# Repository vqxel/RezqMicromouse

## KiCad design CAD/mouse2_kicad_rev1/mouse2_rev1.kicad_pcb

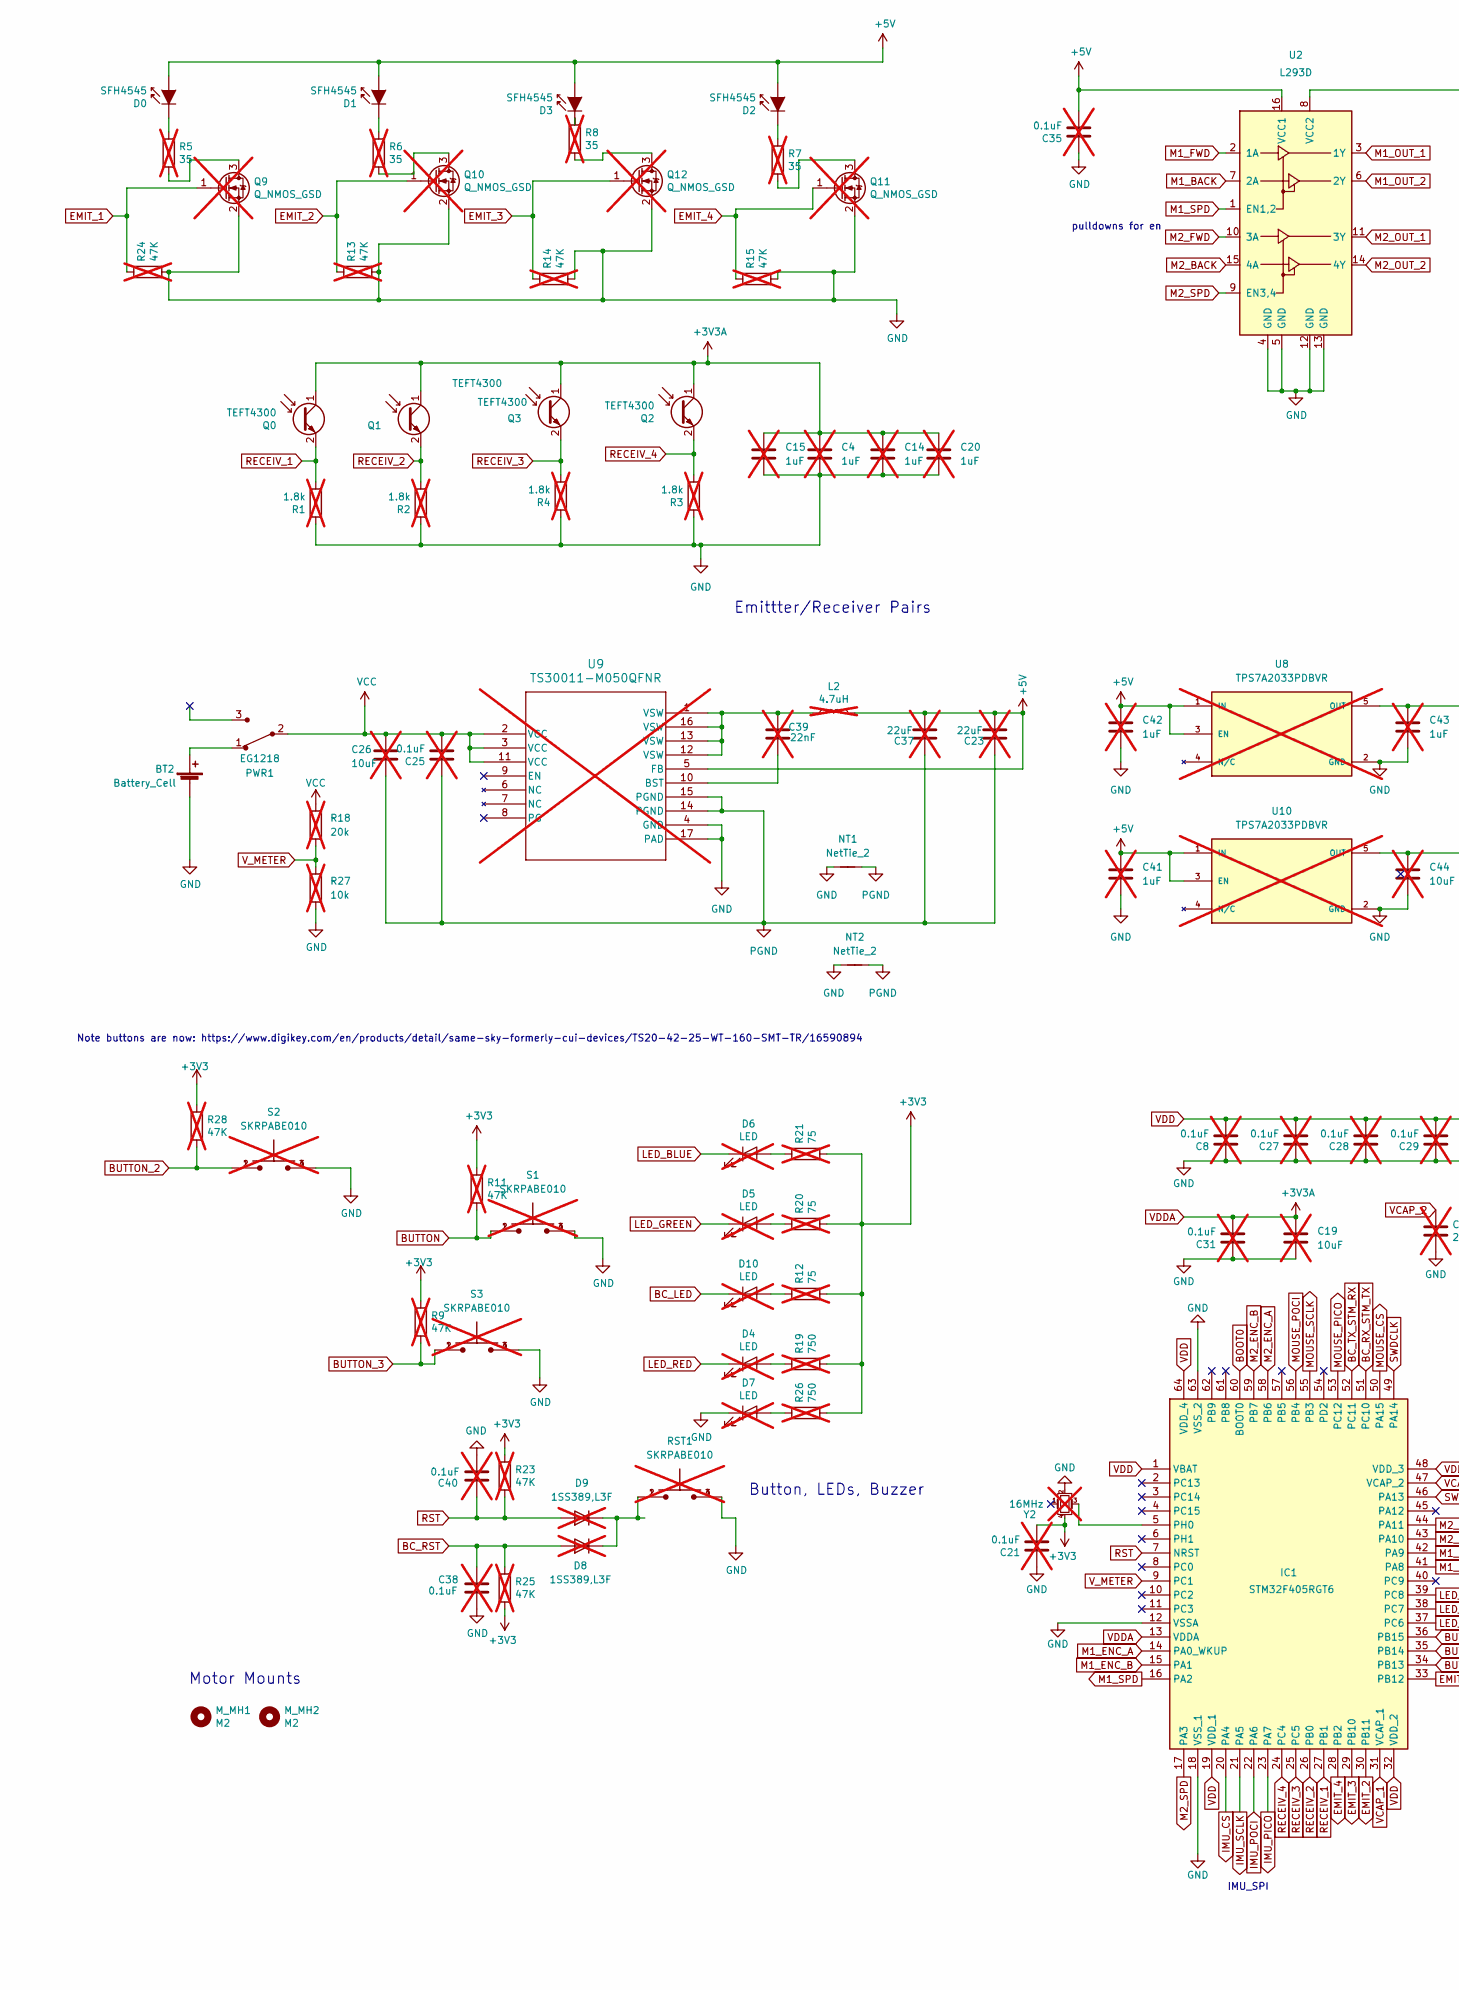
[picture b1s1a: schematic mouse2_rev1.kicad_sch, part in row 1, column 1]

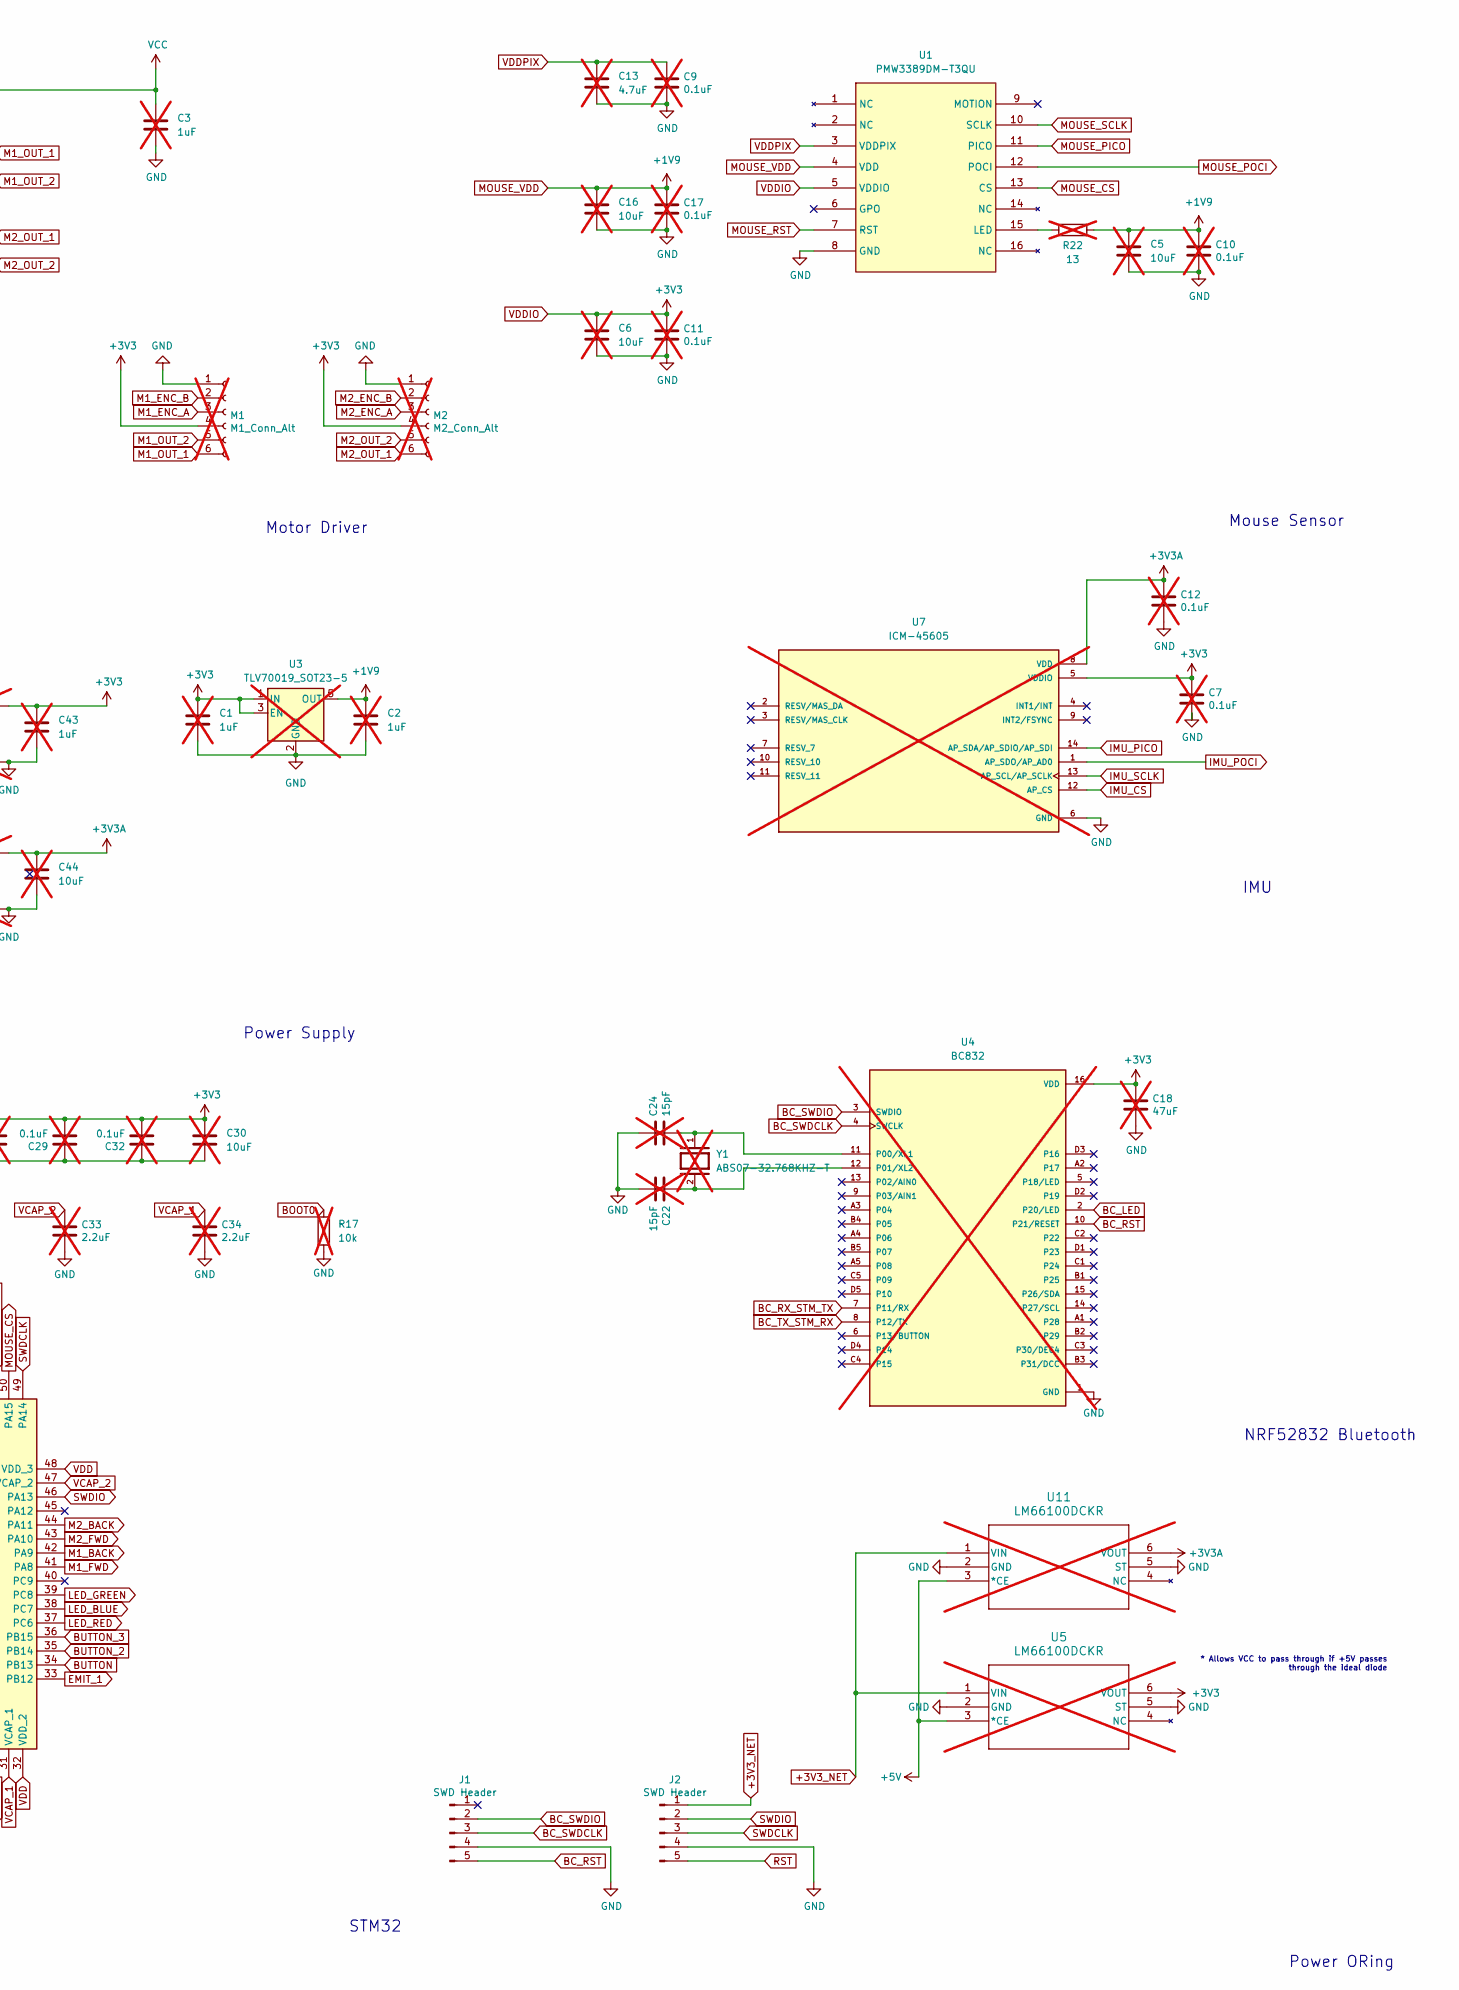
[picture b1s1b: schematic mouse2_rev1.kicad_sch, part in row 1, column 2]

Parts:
BT2: Battery_Cell; PinSocket_1x02_P2.54mm_Vertical
C1, C2, C3, C4, C14, C15, C20, C41, C42, C43: 1uF; C_0603_1608Metric_Pad1.08x0.95mm_HandSolder; not fitted
C5, C6, C16, C19, C26, C30, C44: 10uF; C_0603_1608Metric_Pad1.08x0.95mm_HandSolder; not fitted
C7, C8, C9, C10, C11, C12, C17, C21, C25, C27, C28, C29, C31, C32, C35, C38, C40: 0.1uF; C_0603_1608Metric_Pad1.08x0.95mm_HandSolder; not fitted
C13: 4.7uF; C_0603_1608Metric_Pad1.08x0.95mm_HandSolder; not fitted
C18: 47uF; C_0603_1608Metric_Pad1.08x0.95mm_HandSolder; not fitted
C22, C24: 15pF; C_0603_1608Metric_Pad1.08x0.95mm_HandSolder; not fitted
C23, C37: 22uF; C_0603_1608Metric_Pad1.08x0.95mm_HandSolder; not fitted
C33, C34: 2.2uF; C_0603_1608Metric_Pad1.08x0.95mm_HandSolder; not fitted
C39: 22nF; C_0603_1608Metric_Pad1.08x0.95mm_HandSolder; not fitted
D0, D1, D2, D3: SFH4545; Emitter
D4, D5, D6, D7, D10: LED; LED_0805_2012Metric_Pad1.15x1.40mm_HandSolder; not fitted
D8, D9: 1SS389,L3F; D_SOD-523; not fitted
IC1: STM32F405RGT6; QFP50P1200X1200X160-64N; Manufacturer_Part_Number STM32F405RGT6; Mouser Part Number 511-STM32F405RGT6
J1, J2: SWD Header; PinHeader_1x05_P2.54mm_Vertical
L2: 4.7uH; L_1210_3225Metric_Pad1.42x2.65mm_HandSolder; not fitted
M1: M1_Conn_Alt; JST_SH_BM06B-SRSS-TB_1x06-1MP_P1.00mm_Vertical; not fitted
M2: M2_Conn_Alt; JST_SH_BM06B-SRSS-TB_1x06-1MP_P1.00mm_Vertical; not fitted
M_MH1, M_MH2: M2; Motor_mouse
NT1, NT2: NetTie_2; NetTie-2_SMD_Pad0.5mm
PWR1: EG1218; MM Switch; MPN EG1218; Digi-Key_PN EG1903-ND
Q0, Q1, Q2, Q3: TEFT4300; Emitter
Q9, Q10, Q11, Q12: Q_NMOS_GSD; SOT-23; not fitted
R1, R2, R3, R4: 1.8k; R_0603_1608Metric_Pad0.98x0.95mm_HandSolder; not fitted
R5, R6, R7, R8: 35; R_0603_1608Metric_Pad0.98x0.95mm_HandSolder; not fitted
R9, R11, R13, R14, R15, R23, R24, R25, R28: 47K; R_0603_1608Metric_Pad0.98x0.95mm_HandSolder; not fitted
R12, R20, R21: 75; R_0603_1608Metric_Pad0.98x0.95mm_HandSolder; not fitted
R17, R27: 10k; R_0603_1608Metric_Pad0.98x0.95mm_HandSolder; not fitted
R18: 20k; R_0603_1608Metric_Pad0.98x0.95mm_HandSolder; not fitted
R19, R26: 750; R_0603_1608Metric_Pad0.98x0.95mm_HandSolder; not fitted
R22: 13; R_0603_1608Metric_Pad0.98x0.95mm_HandSolder; not fitted
RST1: SKRPABE010; SW_SKRPABE010; not fitted
S1, S2, S3: SKRPABE010; SW_SKRPABE010; not fitted
U1: PMW3389DM-T3QU; PMW3360DM
U2: L293D; DIP-16_W7.62mm
U3: TLV70019_SOT23-5; SOT-23-5; not fitted
U4: BC832; XCVR_BC832; PARTREV 2.02; not fitted
U5, U11: LM66100DCKR; DCK6_TEX; not fitted
U7: ICM-45605; XDCR_ICM-45605; PARTREV 1.0; DigiKey_Part_Number 1428-ICM-45605CT-ND; not fitted
U8, U10: TPS7A2033PDBVR; SOT95P280X145-5N; PARTREV H; not fitted
U9: TS30011-M050QFNR; QFN16_3X3_SEM; not fitted
Y1: ABS07-32.768KHZ-T; XTAL_ABS07-32.768KHZ-T; PARTREV 08.19.15; not fitted
Y2: 16MHz; Crystal_SMD_2016-4Pin_2.0x1.6mm; Part # ECS-1633-160-BN-TR; not fitted

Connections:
+3V3_NET: J2.1, U5.1 (VIN), U11.1 (VIN)
+5V: C23.1, C35.2, C37.1, C41.1, C42.1, D0.2 (A), D1.2 (A), D2.2 (A), D3.2 (A), L2.2, U2.16 (VCC1), U5.3 (*CE), U8.1 (IN), U8.3 (EN), U9.5 (FB), U10.1 (IN), U10.3 (EN), U11.3 (*CE)
BC_LED: D10.1 (K), U4.2 (P20/LED)
BC_RST: C38.1, D8.2 (A), J1.5, R25.1, U4.10 (P21/RESET)
BC_RX_STM_TX: IC1.51 (PC10), U4.7 (P11/RX)
BC_SWDCLK: J1.3, U4.4 (SWCLK)
BC_SWDIO: J1.2, U4.3 (SWDIO)
BC_TX_STM_RX: IC1.52 (PC11), U4.8 (P12/TX)
BOOT0: IC1.60 (BOOT0), R17.1
BUTTON: IC1.34 (PB13), R11.2, S1.1, S1.2
BUTTON_2: IC1.35 (PB14), R28.2, S2.1, S2.2
BUTTON_3: IC1.36 (PB15), R9.2, S3.1, S3.2
EMIT_1: IC1.33 (PB12), Q9.1 (G), R24.1
EMIT_2: IC1.30 (PB11), Q10.1 (G), R13.1
EMIT_3: IC1.29 (PB10), Q12.1 (G), R14.1
EMIT_4: IC1.28 (PB2), Q11.1 (G), R15.1
GND: BT2.2 (-), C1.2, C2.2, C3.2, C4.2, C5.2, C6.2, C7.2, C8.1, C9.2, C10.2, C11.2, C12.2, C13.2, C14.2, C15.2, C16.2, C17.2, C18.2, C19.2, C20.2, C21.1, C22.2, C24.1, C27.1, C28.1, C29.1, C30.2, C31.1, C32.1, C33.2, C34.2, C35.1, C38.2, C40.2, C41.2, C42.2, C43.2, C44.2, D7.1 (K), IC1.12 (VSSA), IC1.18 (VSS_1), IC1.63 (VSS_2), J1.4, J2.4, M1.1, M2.1, NT1.1, NT2.1, Q9.2 (S), Q10.2 (S), Q11.2 (S), Q12.2 (S), R1.1, R2.1, R3.1, R4.1, R13.2, R14.2, R15.2, R17.2, R24.2, R27.2, RST1.3, RST1.4, S1.3, S1.4, S2.3, S2.4, S3.3, S3.4, U1.8 (GND), U2.4 (GND), U2.5 (GND), U2.12 (GND), U2.13 (GND), U3.2 (GND), U4.1 (GND), U5.2 (GND), U5.5 (ST)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
IMU_CS: IC1.20 (PA4), U7.12 (AP_CS)
IMU_PICO: IC1.23 (PA7), U7.14 (AP_SDA/AP_SDIO/AP_SDI)
IMU_POCI: IC1.22 (PA6), U7.1 (AP_SDO/AP_AD0)
IMU_SCLK: IC1.21 (PA5), U7.13 (AP_SCL/AP_SCLK)
LED_BLUE: D6.1 (K), IC1.38 (PC7)
LED_GREEN: D5.1 (K), IC1.39 (PC8)
LED_RED: D4.1 (K), IC1.37 (PC6)
M1_BACK: IC1.42 (PA9), U2.7 (2A)
M1_ENC_A: IC1.14 (PA0_WKUP), M1.3
M1_ENC_B: IC1.15 (PA1), M1.2
M1_FWD: IC1.41 (PA8), U2.2 (1A)
M1_OUT_1: M1.6, U2.3 (1Y)
M1_OUT_2: M1.5, U2.6 (2Y)
M1_SPD: IC1.16 (PA2), U2.1 (EN1,2)
M2_BACK: IC1.44 (PA11), U2.15 (4A)
M2_ENC_A: IC1.58 (PB6), M2.3
M2_ENC_B: IC1.59 (PB7), M2.2
M2_FWD: IC1.43 (PA10), U2.10 (3A)
M2_OUT_1: M2.6, U2.11 (3Y)
M2_OUT_2: M2.5, U2.14 (4Y)
M2_SPD: IC1.17 (PA3), U2.9 (EN3,4)
MOUSE_CS: IC1.50 (PA15), U1.13 (CS)
MOUSE_PICO: IC1.53 (PC12), U1.11 (PICO)
MOUSE_POCI: IC1.56 (PB4), U1.12 (POCI)
MOUSE_RST: U1.7 (RST)
MOUSE_SCLK: IC1.55 (PB3), U1.10 (SCLK)
MOUSE_VDD: C2.1, C5.1, C10.1, C16.1, C17.1, R22.2, U1.4 (VDD), U3.5 (OUT)
unnamed: BT2.1 (+), PWR1.1
unnamed: C39.2, L2.1, U9.1 (VSW), U9.12 (VSW), U9.13 (VSW), U9.16 (VSW)
unnamed: D0.1 (K), R5.1
unnamed: D1.1 (K), R6.1
unnamed: D2.1 (K), R7.1
unnamed: D3.1 (K), R8.1
unnamed: D4.2 (A), R19.1
unnamed: D5.2 (A), R20.1
unnamed: D6.2 (A), R21.1
unnamed: D7.2 (A), R26.1
unnamed: D8.1 (K), D9.1 (K), RST1.1, RST1.2
unnamed: D10.2 (A), R12.1
unnamed: IC1.5 (PH0), Y2.3
unnamed: Q9.3 (D), R5.2
unnamed: Q10.3 (D), R6.2
unnamed: Q11.3 (D), R7.2
unnamed: Q12.3 (D), R8.2
unnamed: R22.1, U1.15 (LED)
unnamed: C24.2, U4.11 (P00/XL1), Y1.1
unnamed: C22.1, U4.12 (P01/XL2), Y1.2
unnamed: C39.1, U9.10 (BST)
PGND: C23.2, C25.1, C26.2, C37.2, NT1.2, NT2.2, U9.14 (PGND), U9.15 (PGND)
RECEIV_1: IC1.27 (PB1), Q0.2 (E), R1.2
RECEIV_2: IC1.26 (PB0), Q1.2 (E), R2.2
RECEIV_3: IC1.25 (PC5), Q3.2 (E), R4.2
RECEIV_4: IC1.24 (PC4), Q2.2 (E), R3.2
RST: C40.1, D9.2 (A), IC1.7 (NRST), J2.5, R23.2
SWDCLK: IC1.49 (PA14), J2.3
SWDIO: IC1.46 (PA13), J2.2
VCAP_1: C34.1, IC1.31 (VCAP_1)
VCAP_2: C33.1, IC1.47 (VCAP_2)
VCC: C3.1, C25.2, C26.1, PWR1.2, R18.1, U2.8 (VCC2), U9.2 (VCC), U9.3 (VCC), U9.11 (VCC)
VDD: C1.1, C6.1, C7.1, C8.2, C11.1, C18.1, C21.2, C27.2, C28.2, C29.2, C30.1, C32.2, C43.1, IC1.1 (VBAT), IC1.19 (VDD_1), IC1.32 (VDD_2), IC1.48 (VDD_3), IC1.64 (VDD_4), M1.4, M2.4, R9.1, R11.1, R12.2, R19.2, R20.2, R21.2, R23.1, R25.2, R26.2, R28.1, U1.5 (VDDIO), U3.1 (IN), U3.3 (EN), U4.16 (VDD), U5.6 (VOUT), U7.5 (VDDIO), U8.5 (OUT), Y2.4
VDDA: C4.1, C12.1, C14.1, C15.1, C19.1, C20.1, C31.2, C44.1, IC1.13 (VDDA), Q0.1 (C), Q1.1 (C), Q2.1 (C), Q3.1 (C), U7.8 (VDD), U10.5 (OUT), U11.6 (VOUT)
VDDPIX: C9.1, C13.1, U1.3 (VDDPIX)
V_METER: IC1.9 (PC1), R18.2, R27.1

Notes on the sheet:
Mouse Sensor
IMU_SPI
Power ORing
STM32
pulldowns for en
Motor Driver
* Allows VCC to pass through if +5V passes through the ideal diode
Emittter/Receiver Pairs
NRF52832 Bluetooth
Note buttons are now: https://www.digikey.com/en/products/detail/same-sky-formerly-cui-devices/TS20-42-25-WT-160-SMT-TR/16590894
IMU
Motor Mounts
Button, LEDs, Buzzer
Power Supply

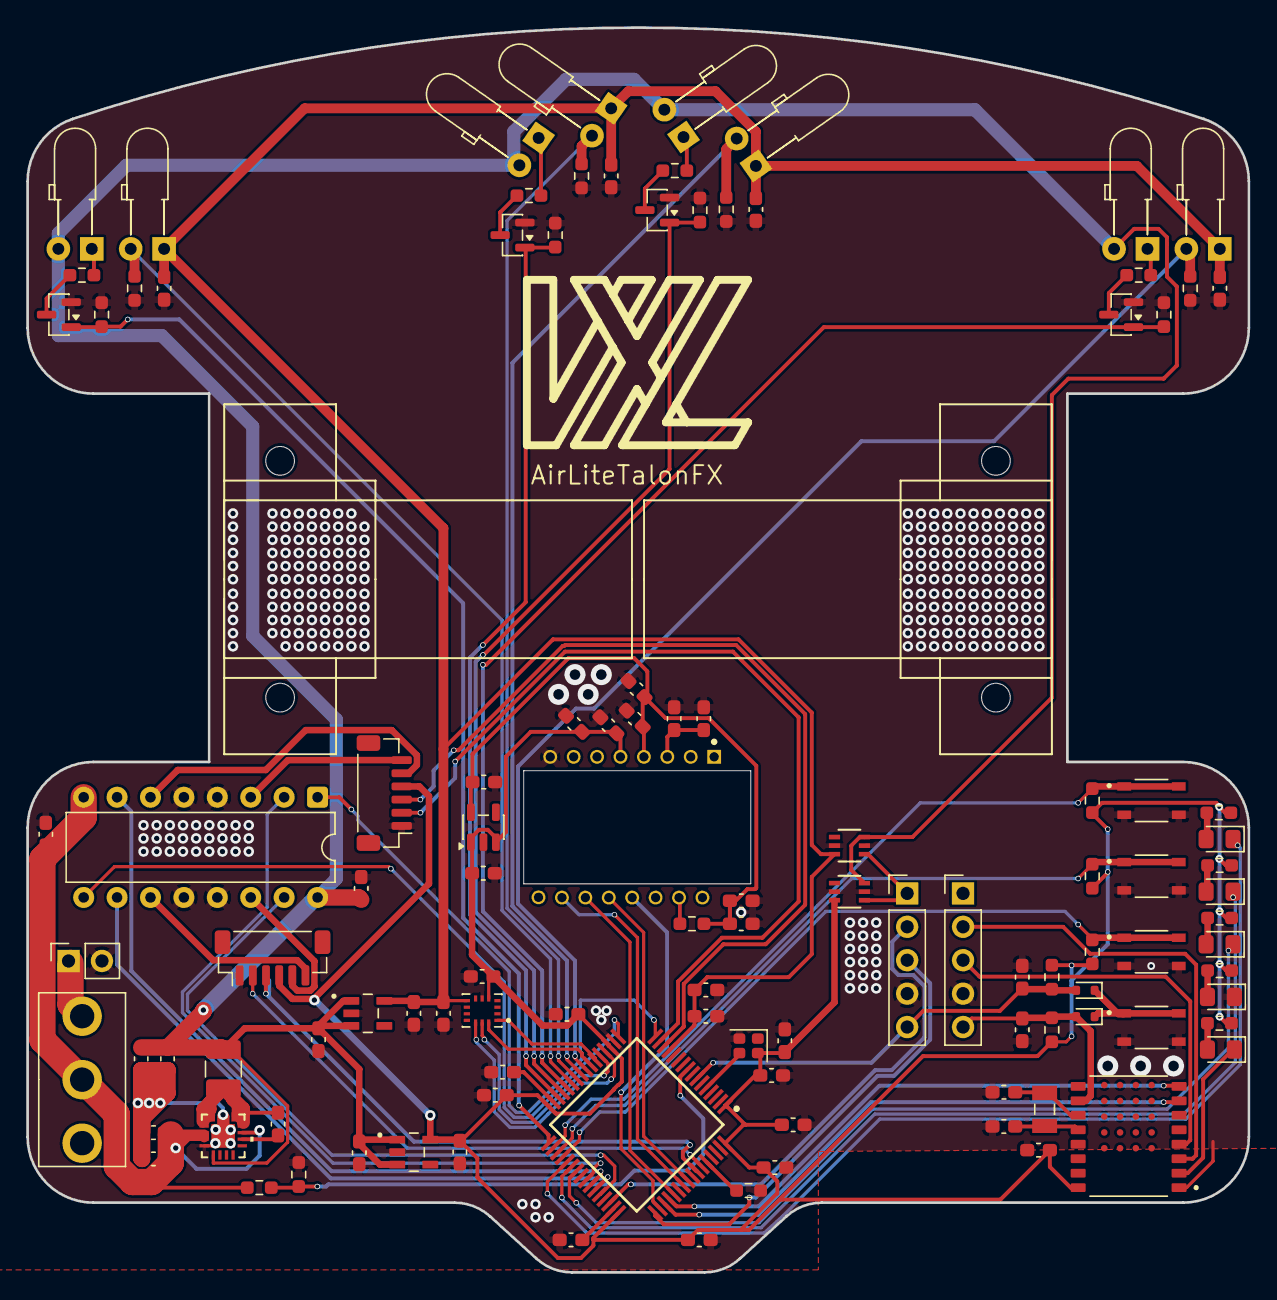
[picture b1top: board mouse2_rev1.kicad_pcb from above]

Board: 2 copper layers, 92.8 x 94.6 mm, 116 parts (0 on the bottom side), 79 nets.

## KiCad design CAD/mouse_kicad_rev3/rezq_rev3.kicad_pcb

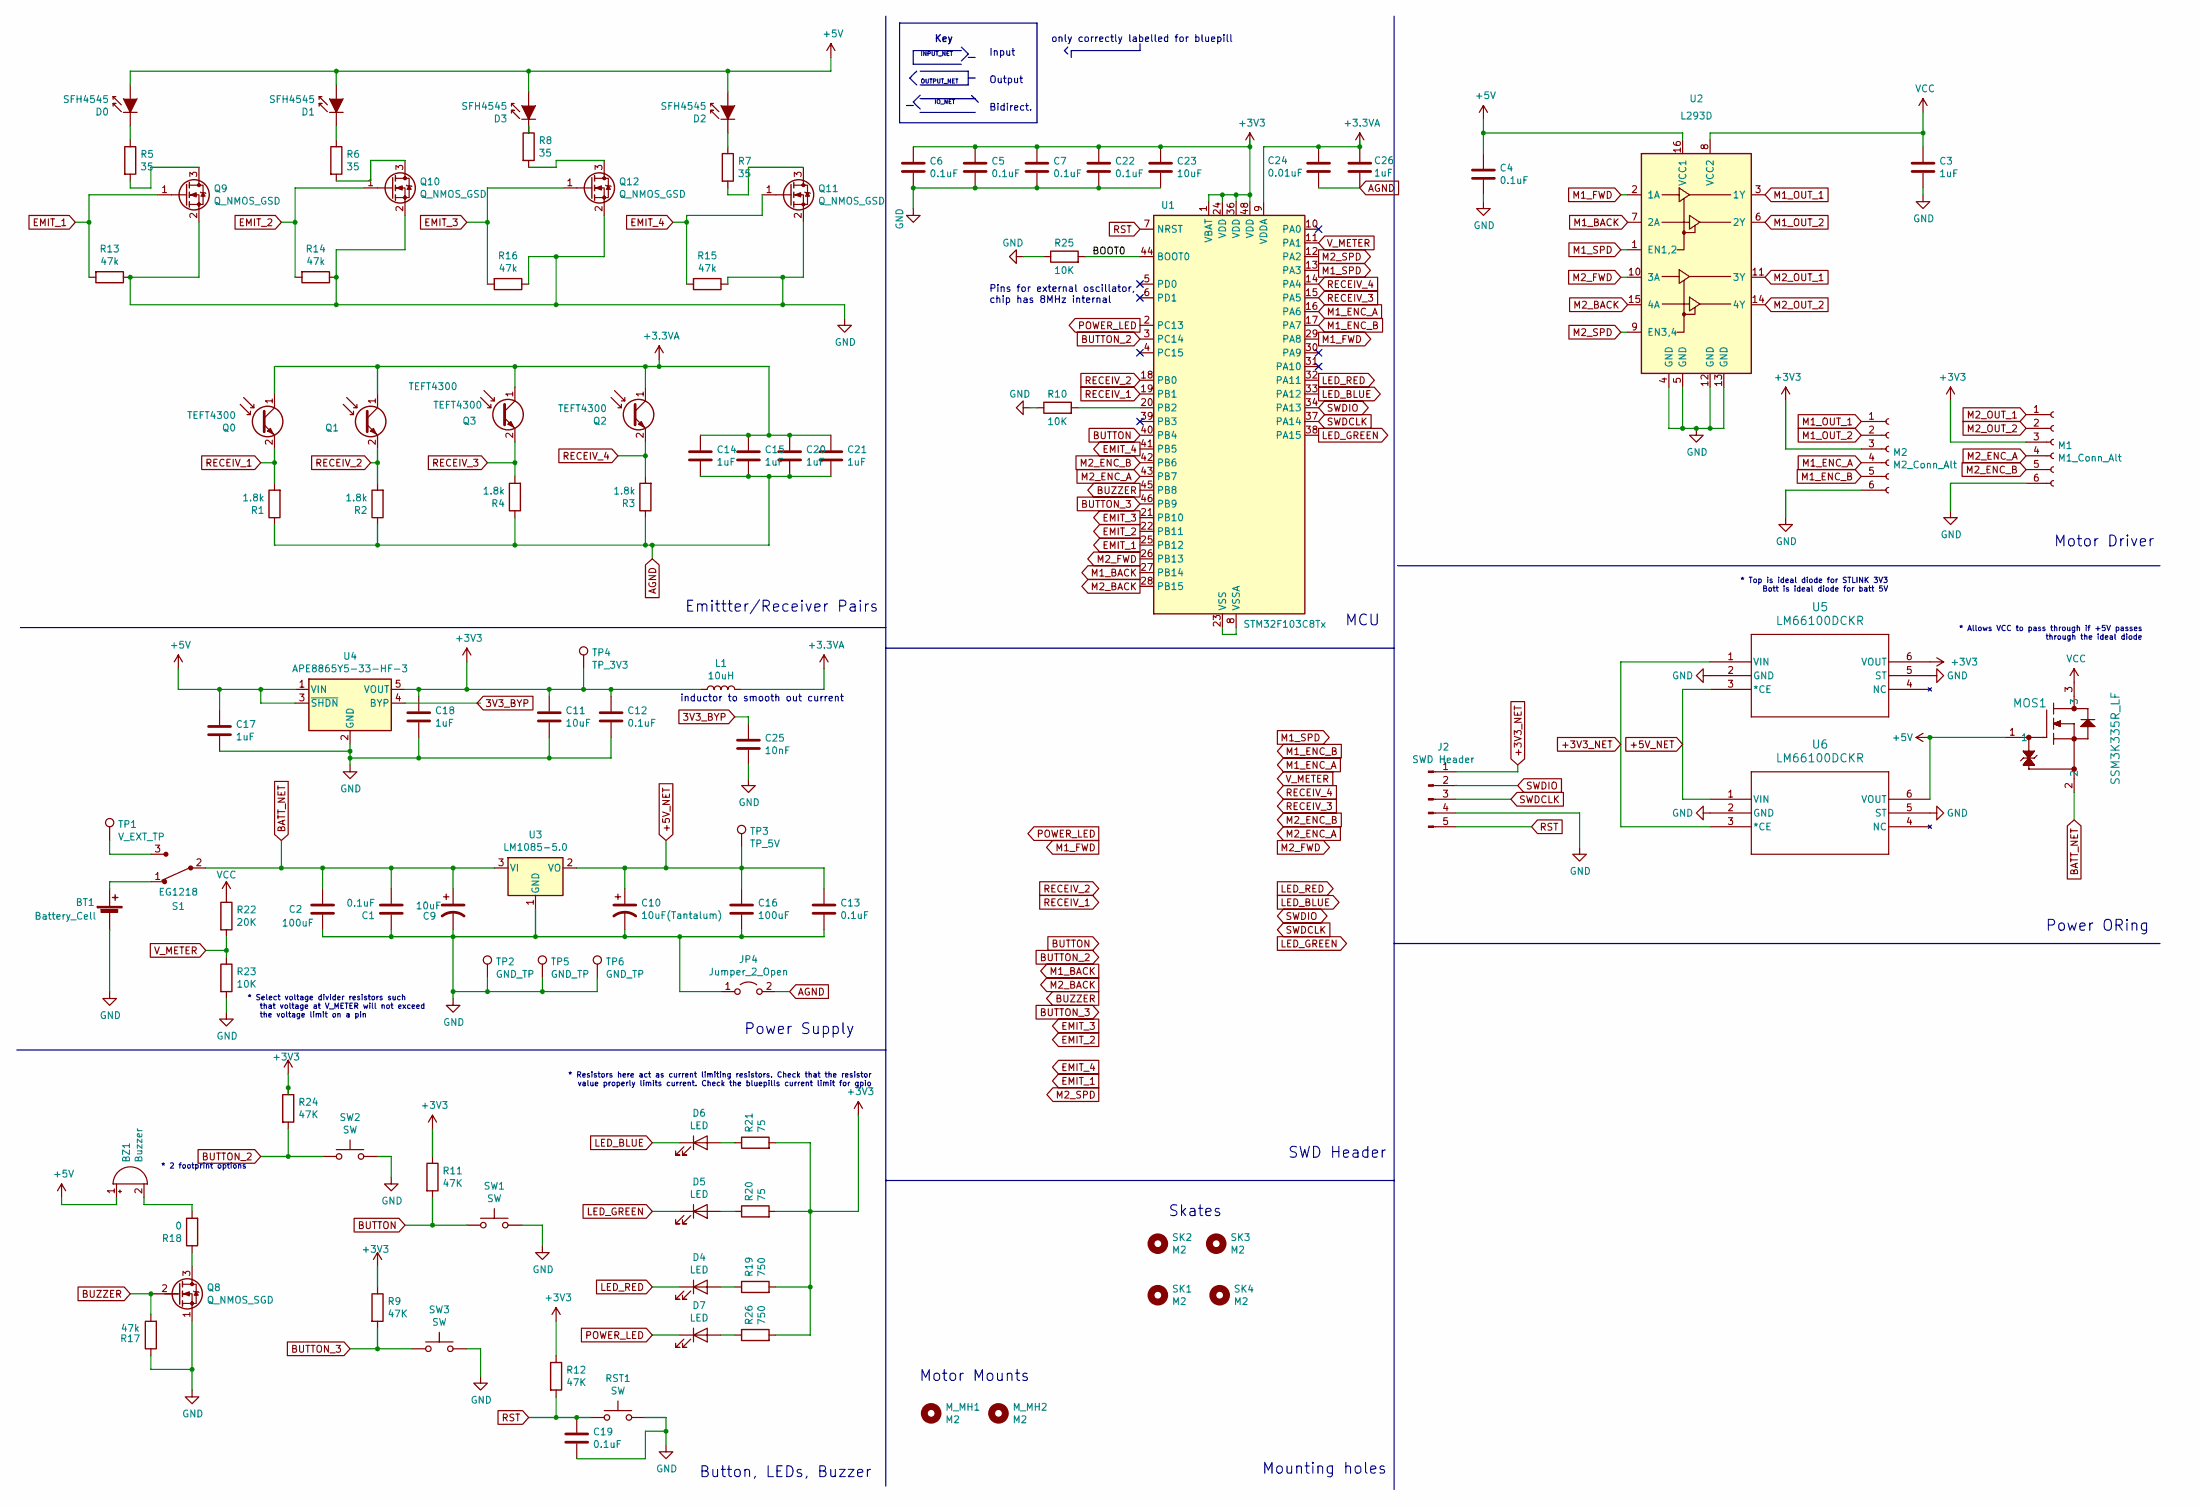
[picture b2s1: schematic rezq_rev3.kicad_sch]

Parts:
BT1: Battery_Cell; PinSocket_1x02_P2.54mm_Vertical
BZ1: Buzzer; MagneticBuzzer_PUI_AT-0927-TT-6-R
C1, C4, C5, C6, C7, C12, C13, C19, C22: 0.1uF; C_1206_3216Metric_Pad1.33x1.80mm_HandSolder
C2, C16: 100uF; CP_Radial_D6.3mm_P2.50mm
C3, C14, C15, C17, C18, C20, C21, C26: 1uF; C_1206_3216Metric_Pad1.33x1.80mm_HandSolder
C9, C11, C23: 10uF; C_1206_3216Metric_Pad1.33x1.80mm_HandSolder
C10: 10uF(Tantalum); C_1206_3216Metric_Pad1.33x1.80mm_HandSolder
C24: 0.01uF; C_1206_3216Metric_Pad1.33x1.80mm_HandSolder
C25: 10nF; C_1206_3216Metric_Pad1.33x1.80mm_HandSolder
D0, D1, D2, D3: SFH4545; Emitter
D4, D5, D6, D7: LED; LED_0805_2012Metric_Pad1.15x1.40mm_HandSolder
J2: SWD Header; PinHeader_1x05_P2.54mm_Vertical
JP4: Jumper_2_Open; SolderJumper-2_P1.3mm_Bridged_Pad1.0x1.5mm
L1: 10uH; L_1206_3216Metric_Pad1.42x1.75mm_HandSolder
M1: M1_Conn_Alt; JST_SH_BM06B-SRSS-TB_1x06-1MP_P1.00mm_Vertical
M2: M2_Conn_Alt; JST_SH_BM06B-SRSS-TB_1x06-1MP_P1.00mm_Vertical
MOS1: SSM3K335R_LF; SOT-23F_TOS
M_MH1, M_MH2: M2; Motor_mouse
Q0, Q1, Q2, Q3: TEFT4300; Emitter
Q8: Q_NMOS_SGD; SOT-23
Q9, Q10, Q11, Q12: Q_NMOS_GSD; SOT-23
R1, R2, R3, R4: 1.8k; R_1206_3216Metric_Pad1.30x1.75mm_HandSolder
R5, R6, R7, R8: 35; R_1206_3216Metric_Pad1.30x1.75mm_HandSolder
R9, R11, R12, R24: 47K; R_1206_3216Metric_Pad1.30x1.75mm_HandSolder
R10, R23, R25: 10K; R_1206_3216Metric_Pad1.30x1.75mm_HandSolder
R13, R14, R15, R16, R17: 47k; R_1206_3216Metric_Pad1.30x1.75mm_HandSolder
R18: 0; R_1206_3216Metric_Pad1.30x1.75mm_HandSolder
R19, R26: 750; R_1206_3216Metric_Pad1.30x1.75mm_HandSolder
R20, R21: 75; R_1206_3216Metric_Pad1.30x1.75mm_HandSolder
R22: 20K; R_1206_3216Metric_Pad1.30x1.75mm_HandSolder
RST1: SW; SW_SPST_REED_CT05-XXXX-G1
S1: EG1218; MM Switch; MPN EG1218; Digi-Key_PN EG1903-ND
SK1, SK2, SK3, SK4: M2; MountingHole_2.2mm_M2
SW1, SW2, SW3: SW; SW_SPST_REED_CT05-XXXX-G1
TP1: V_EXT_TP; PinHeader_1x01_P2.54mm_Vertical
TP2, TP5, TP6: GND_TP; PinHeader_1x01_P2.54mm_Vertical
TP3: TP_5V; PinHeader_1x01_P2.54mm_Vertical
TP4: TP_3V3; PinHeader_1x01_P2.54mm_Vertical
U1: STM32F103C8Tx; LQFP-48_7x7mm_P0.5mm
U2: L293D; DIP-16_W7.62mm
U3: LM1085-5.0; 5V Voltage Reg
U4: APE8865Y5-33-HF-3; SOT-23-5
U5, U6: LM66100DCKR; DCK6_TEX

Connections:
3V3_BYP: C25.1, U4.4 (BYP)
+3.3VA: C14.1, C15.1, C20.1, C21.1, C24.1, C26.1, L1.2, Q0.1 (C), Q1.1 (C), Q2.1 (C), Q3.1 (C), U1.9 (VDDA)
+3V3: C5.1, C6.1, C7.1, C11.1, C12.1, C18.1, C22.1, C23.1, L1.1, M1.3, M2.3, R9.1, R11.1, R12.1, R19.2, R20.2, R21.2, R24.1, R26.2, TP4.1, U1.1 (VBAT), U1.24 (VDD), U1.36 (VDD), U1.48 (VDD), U4.5 (VOUT), U5.6 (VOUT)
+3V3_NET: J2.1, U5.1 (VIN), U6.3 (*CE)
+5V: BZ1.1 (-), C4.1, C17.1, D0.2 (A), D1.2 (A), D2.2 (A), D3.2 (A), MOS1.1, U2.16 (VCC1), U4.1 (VIN), U4.3 (~SHDN), U6.6 (VOUT)
+5V_NET: C10.1, C13.1, C16.1, TP3.1, U3.2 (VO), U5.3 (*CE), U6.1 (VIN)
/BOOT0: R25.2, U1.44 (BOOT0)
AGND: C14.2, C15.2, C20.2, C21.2, C24.2, C26.2, JP4.2 (B), R1.1, R2.1, R3.1, R4.1
BATT_NET: C1.2, C2.1, C9.1, MOS1.2, S1.2, U3.3 (VI)
BUTTON: R11.2, SW1.1, U1.40 (PB4)
BUTTON_2: R24.2, SW2.1, U1.3 (PC14)
BUTTON_3: R9.2, SW3.1, U1.46 (PB9)
BUZZER: Q8.2 (G), R17.2, U1.45 (PB8)
EMIT_1: Q9.1 (G), R13.2, U1.25 (PB12)
EMIT_2: Q10.1 (G), R14.2, U1.22 (PB11)
EMIT_3: Q12.1 (G), R16.2, U1.21 (PB10)
EMIT_4: Q11.1 (G), R15.2, U1.41 (PB5)
GND: BT1.2 (-), C1.1, C2.2, C3.2, C4.2, C5.2, C6.2, C7.2, C9.2, C10.2, C11.2, C12.2, C13.2, C16.2, C17.2, C18.2, C19.2, C22.2, C23.2, C25.2, J2.4, JP4.1 (A), M1.6, M2.6, Q8.1 (S), Q9.2 (S), Q10.2 (S), Q11.2 (S), Q12.2 (S), R10.1, R13.1, R14.1, R15.1, R16.1, R17.1, R23.2, R25.1, RST1.2, SW1.2, SW2.2, SW3.2, TP2.1, TP5.1, TP6.1, U2.4 (GND), U2.5 (GND), U2.12 (GND), U2.13 (GND), U3.1 (GND), U4.2 (GND), U5.2 (GND), U5.5 (ST), U6.2 (GND), U6.5 (ST)
LED_BLUE: D6.1 (K), U1.33 (PA12)
LED_GREEN: D5.1 (K), U1.38 (PA15)
LED_RED: D4.1 (K), U1.32 (PA11)
M1_BACK: U1.27 (PB14), U2.7 (2A)
M1_ENC_A: M2.4, U1.16 (PA6)
M1_ENC_B: M2.5, U1.17 (PA7)
M1_FWD: U1.29 (PA8), U2.2 (1A)
M1_OUT_1: M2.1, U2.3 (1Y)
M1_OUT_2: M2.2, U2.6 (2Y)
M1_SPD: U1.13 (PA3), U2.1 (EN1,2)
M2_BACK: U1.28 (PB15), U2.15 (4A)
M2_ENC_A: M1.4, U1.43 (PB7)
M2_ENC_B: M1.5, U1.42 (PB6)
M2_FWD: U1.26 (PB13), U2.10 (3A)
M2_OUT_1: M1.1, U2.11 (3Y)
M2_OUT_2: M1.2, U2.14 (4Y)
M2_SPD: U1.12 (PA2), U2.9 (EN3,4)
unnamed: BT1.1 (+), S1.1
unnamed: BZ1.2 (+), R18.2
unnamed: D0.1 (K), R5.1
unnamed: D1.1 (K), R6.1
unnamed: D2.1 (K), R7.1
unnamed: D3.1 (K), R8.1
unnamed: D4.2 (A), R19.1
unnamed: D5.2 (A), R20.1
unnamed: D6.2 (A), R21.1
unnamed: D7.2 (A), R26.1
unnamed: Q8.3 (D), R18.1
unnamed: Q9.3 (D), R5.2
unnamed: Q10.3 (D), R6.2
unnamed: Q11.3 (D), R7.2
unnamed: Q12.3 (D), R8.2
unnamed: S1.3, TP1.1
unnamed: R10.2, U1.20 (PB2)
unnamed: U1.8 (VSSA), U1.23 (VSS), U1.35 (VSS), U1.47 (VSS)
POWER_LED: D7.1 (K), U1.2 (PC13)
RECEIV_1: Q0.2 (E), R1.2, U1.19 (PB1)
RECEIV_2: Q1.2 (E), R2.2, U1.18 (PB0)
RECEIV_3: Q3.2 (E), R4.2, U1.15 (PA5)
RECEIV_4: Q2.2 (E), R3.2, U1.14 (PA4)
RST: C19.1, J2.5, R12.2, RST1.1, U1.7 (NRST)
SWDCLK: J2.3, U1.37 (PA14)
SWDIO: J2.2, U1.34 (PA13)
VCC: C3.1, MOS1.3, R22.1, U2.8 (VCC2)
V_METER: R22.2, R23.1, U1.11 (PA1)

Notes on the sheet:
Pins for external oscillator, chip has 8MHz internal
Mounting holes
Output
IO_NET
Power ORing
Input
inductor to smooth out current
* 2 footprint options
* Top is ideal diode for STLINK 3V3 Bott is ideal diode for batt 5V
Motor Driver
* Allows VCC to pass through if +5V passes through the ideal diode
Emittter/Receiver Pairs
* Resistors here act as current limiting resistors. Check that the resistor value properly limits current. Check the bluepills current limit for gpio
Bidirect.
MCU
OUTPUT_NET
SWD Header
only correctly labelled for bluepill
* Select voltage divider resistors such that voltage at V_METER will not exceed the voltage limit on a pin
Motor Mounts
Button, LEDs, Buzzer
Skates
Power Supply
Key
INPUT_NET

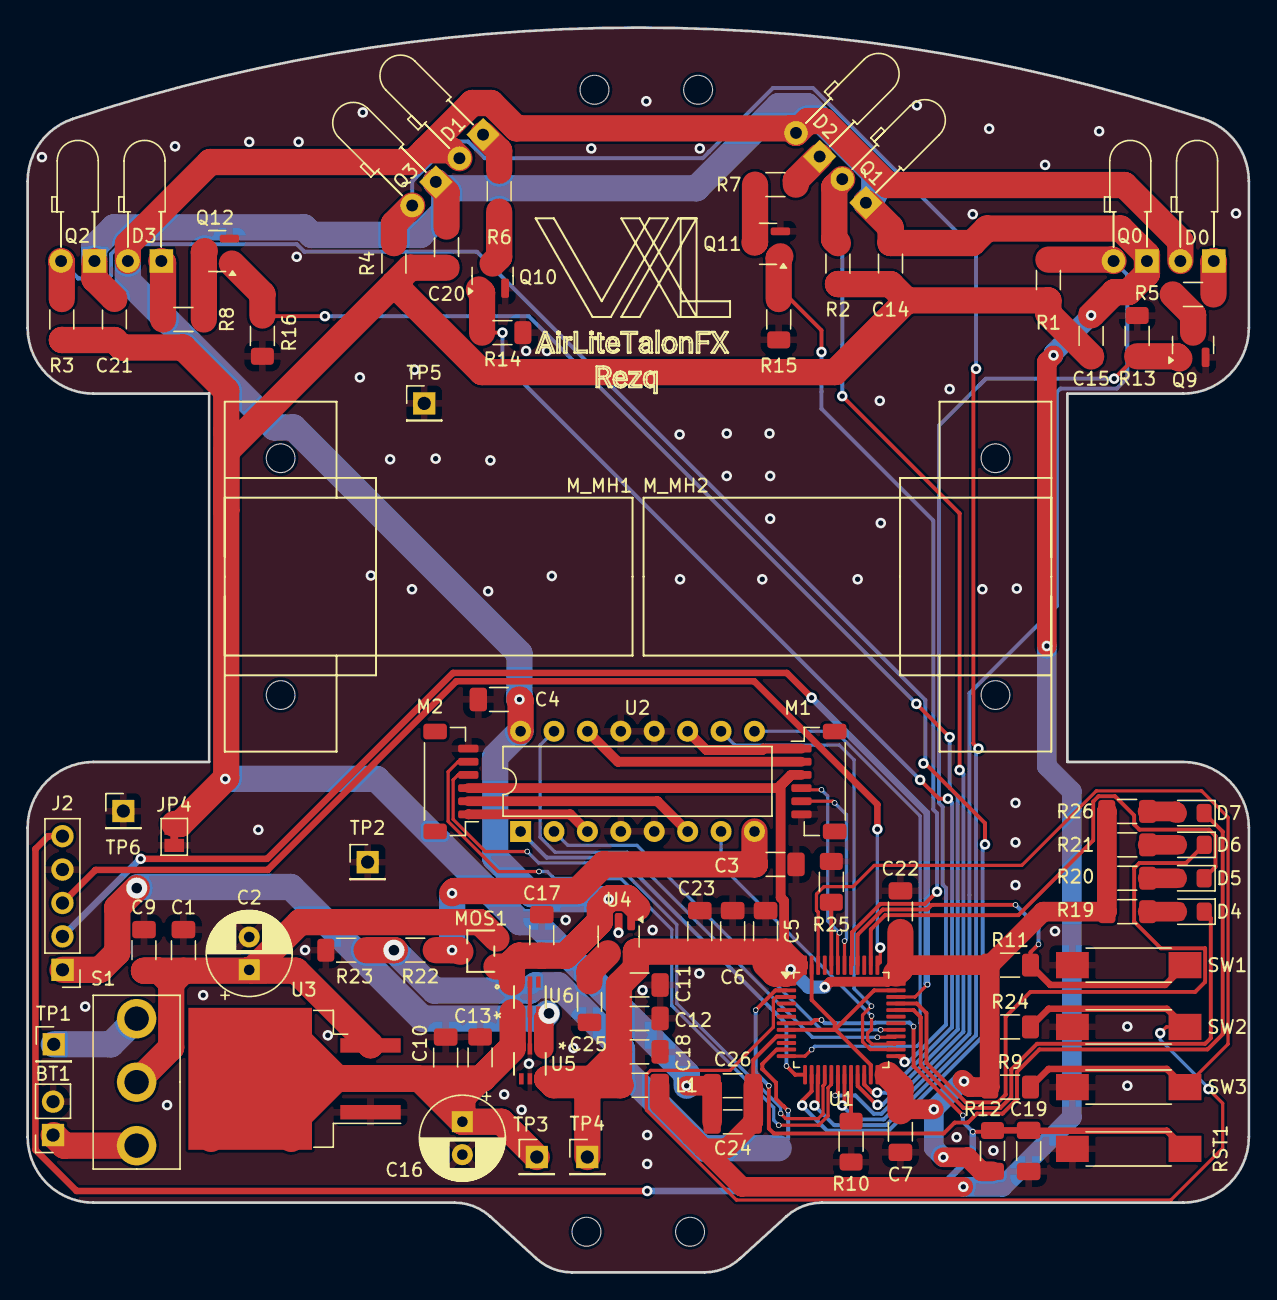
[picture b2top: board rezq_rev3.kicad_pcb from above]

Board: 2 copper layers, 92.8 x 94.6 mm, 95 parts (0 on the bottom side), 60 nets.

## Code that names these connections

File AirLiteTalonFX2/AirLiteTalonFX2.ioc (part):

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Mcu.Name=STM32F405RGTx
Mcu.Package=LQFP64
Mcu.UserName=STM32F405RGTx
PA0-WKUP.GPIOParameters=GPIO_Label
PA0-WKUP.GPIO_Label=M1_ENC_A
PA0-WKUP.Signal=S_TIM2_CH1_ETR
PA1.GPIOParameters=GPIO_Label
PA1.GPIO_Label=M1_ENC_B
PA1.Signal=S_TIM2_CH2
PA10.GPIOParameters=GPIO_Label
PA10.GPIO_Label=M2_FWD
PA10.Signal=GPIO_Output
PA11.GPIOParameters=GPIO_Label
PA11.GPIO_Label=M2_BACK
PA11.Signal=GPIO_Output
PA13.Mode=Serial_Wire
PA13.Signal=SYS_JTMS-SWDIO
PA14.Mode=Serial_Wire
PA14.Signal=SYS_JTCK-SWCLK
PA15.GPIOParameters=GPIO_Label
PA15.GPIO_Label=MOUSE_CS
PA15.Signal=GPIO_Output
PA2.GPIOParameters=GPIO_Label
PA2.GPIO_Label=M1_SPD
PA2.Signal=S_TIM5_CH3
PA3.GPIOParameters=GPIO_Label
PA3.GPIO_Label=M2_SPD
PA3.Signal=S_TIM5_CH4
PA4.GPIOParameters=GPIO_Label
PA4.GPIO_Label=IMU_CS
PA4.Signal=GPIO_Output
PA5.GPIOParameters=GPIO_Label
PA5.GPIO_Label=IMU_SCLK
PA5.Mode=Full_Duplex_Master
PA5.Signal=SPI1_SCK
PA6.GPIOParameters=GPIO_PuPd,GPIO_Label
PA6.GPIO_Label=IMU_POCI
PA6.GPIO_PuPd=GPIO_PULLUP
PA6.Mode=Full_Duplex_Master
PA6.Signal=SPI1_MISO
PA7.GPIOParameters=GPIO_Label
PA7.GPIO_Label=IMU_PICO
PA7.Mode=Full_Duplex_Master
PA7.Signal=SPI1_MOSI
PA8.GPIOParameters=GPIO_Label
PA8.GPIO_Label=M1_FWD
PA8.Signal=GPIO_Output
PA9.GPIOParameters=GPIO_Label
PA9.GPIO_Label=M1_BACK
PA9.Signal=GPIO_Output
PB0.GPIOParameters=GPIO_Label
PB0.GPIO_Label=RECEIV_2
PB0.Signal=ADCx_IN8
PB1.GPIOParameters=GPIO_Label
PB1.GPIO_Label=RECEIV_1
PB1.Signal=ADCx_IN9
PB10.GPIOParameters=GPIO_Label
PB10.GPIO_Label=EMIT_3
PB10.Signal=GPIO_Output
PB11.GPIOParameters=GPIO_Label
PB11.GPIO_Label=EMIT_2
PB11.Signal=GPIO_Output
PB12.GPIOParameters=GPIO_Label
PB12.GPIO_Label=EMIT_1
PB12.Signal=GPIO_Output
PB13.GPIOParameters=GPIO_Label
PB13.GPIO_Label=BUTTON_1
PB13.Signal=GPIO_Input
PB14.GPIOParameters=GPIO_Label
PB14.GPIO_Label=BUTTON_2
PB14.Signal=GPIO_Input
PB15.GPIOParameters=GPIO_Label
PB15.GPIO_Label=BUTTON_3
PB15.Signal=GPIO_Input
PB2.GPIOParameters=GPIO_Label
PB2.GPIO_Label=EMIT_4
PB2.Signal=GPIO_Output
PB3.GPIOParameters=GPIO_Label
PB3.GPIO_Label=MOUSE_SCLK
PB3.Mode=Full_Duplex_Master
PB3.Signal=SPI3_SCK
PB4.GPIOParameters=GPIO_PuPd,GPIO_Label
PB4.GPIO_Label=MOUSE_POCI
PB4.GPIO_PuPd=GPIO_PULLUP
PB4.Mode=Full_Duplex_Master
PB4.Signal=SPI3_MISO
PB6.GPIOParameters=GPIO_Label
PB6.GPIO_Label=M2_ENC_A
PB6.Signal=S_TIM4_CH1
PB7.GPIOParameters=GPIO_Label
PB7.GPIO_Label=M2_ENC_B
PB7.Signal=S_TIM4_CH2
PC1.GPIOParameters=GPIO_Label
PC1.GPIO_Label=V_METER
PC1.Signal=ADCx_IN11
PC10.GPIOParameters=GPIO_Label
PC10.GPIO_Label=BC_TX
PC10.Mode=Asynchronous
PC10.Signal=UART4_TX
PC11.GPIOParameters=GPIO_Label
PC11.GPIO_Label=BC_RX
PC11.Mode=Asynchronous
PC11.Signal=UART4_RX
PC12.GPIOParameters=GPIO_Label
PC12.GPIO_Label=MOUSE_PICO
PC12.Mode=Full_Duplex_Master
PC12.Signal=SPI3_MOSI
PC4.GPIOParameters=GPIO_Label
PC4.GPIO_Label=RECEIV_4
PC4.Signal=ADCx_IN14
PC5.GPIOParameters=GPIO_Label
PC5.GPIO_Label=RECEIV_3
PC5.Signal=ADCx_IN15
PC6.GPIOParameters=PinState,GPIO_PuPd,GPIO_Label,GPIO_ModeDefaultOutputPP
PC6.GPIO_Label=LED_RED
PC6.GPIO_ModeDefaultOutputPP=GPIO_MODE_OUTPUT_OD
PC6.GPIO_PuPd=GPIO_PULLUP
PC6.PinState=GPIO_PIN_SET
PC6.Signal=GPIO_Output
PC7.GPIOParameters=PinState,GPIO_PuPd,GPIO_Label,GPIO_ModeDefaultOutputPP
PC7.GPIO_Label=LED_BLUE
PC7.GPIO_ModeDefaultOutputPP=GPIO_MODE_OUTPUT_OD
PC7.GPIO_PuPd=GPIO_PULLUP
PC7.PinState=GPIO_PIN_SET
PC7.Signal=GPIO_Output
PC8.GPIOParameters=PinState,GPIO_PuPd,GPIO_Label,GPIO_ModeDefaultOutputPP
PC8.GPIO_Label=LED_GREEN
PC8.GPIO_ModeDefaultOutputPP=GPIO_MODE_OUTPUT_OD
PC8.GPIO_PuPd=GPIO_PULLUP
PC8.PinState=GPIO_PIN_SET
PC8.Signal=GPIO_Output
PH0-OSC_IN.Mode=HSE-External-Clock-Source
PH0-OSC_IN.Signal=RCC_OSC_IN
PH1-OSC_OUT.Mode=HSE-External-Clock-Source
PH1-OSC_OUT.Signal=RCC_OSC_OUT
RCC.HSE_VALUE=25000000
RCC.SYSCLKFreq_VALUE=16000000
board=custom

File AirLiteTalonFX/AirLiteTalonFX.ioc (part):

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Mcu.Name=STM32F103C(8-B)Tx
Mcu.Package=LQFP48
Mcu.UserName=STM32F103C8Tx
PA1.GPIOParameters=GPIO_Label
PA1.GPIO_Label=V_METER
PA1.Signal=ADCx_IN1
PA11.GPIOParameters=GPIO_PuPd,GPIO_Label
PA11.GPIO_Label=LED_RED
PA11.GPIO_PuPd=GPIO_PULLUP
PA11.Signal=GPIO_Output
PA12.GPIOParameters=GPIO_PuPd,GPIO_Label
PA12.GPIO_Label=LED_BLUE
PA12.GPIO_PuPd=GPIO_PULLUP
PA12.Signal=GPIO_Output
PA13.Mode=Serial_Wire
PA13.Signal=SYS_JTMS-SWDIO
PA14.Mode=Serial_Wire
PA14.Signal=SYS_JTCK-SWCLK
PA15.GPIOParameters=GPIO_PuPd,GPIO_Label
PA15.GPIO_Label=LED_GREEN
PA15.GPIO_PuPd=GPIO_PULLUP
PA15.Signal=GPIO_Output
PA2.GPIOParameters=GPIO_Label
PA2.GPIO_Label=M2_SPD
PA2.Signal=S_TIM2_CH3
PA3.GPIOParameters=GPIO_Label
PA3.GPIO_Label=M1_SPD
PA3.Signal=S_TIM2_CH4
PA4.GPIOParameters=GPIO_Label
PA4.GPIO_Label=RCV_4
PA4.Signal=ADCx_IN4
PA5.GPIOParameters=GPIO_Label
PA5.GPIO_Label=RCV_3
PA5.Signal=ADCx_IN5
PA6.GPIOParameters=GPIO_Label
PA6.GPIO_Label=M1_ENC_A
PA6.Signal=S_TIM3_CH1
PA7.GPIOParameters=GPIO_Label
PA7.GPIO_Label=M1_ENC_B
PA7.Signal=S_TIM3_CH2
PA8.GPIOParameters=GPIO_Label
PA8.GPIO_Label=M1_FWD
PA8.Signal=GPIO_Output
PB0.GPIOParameters=GPIO_Label
PB0.GPIO_Label=RCV_2
PB0.Signal=ADCx_IN8
PB1.GPIOParameters=GPIO_Label
PB1.GPIO_Label=RCV_1
PB1.Signal=ADCx_IN9
PB10.GPIOParameters=GPIO_Label
PB10.GPIO_Label=EMIT_3
PB10.Signal=GPIO_Output
PB11.GPIOParameters=GPIO_Label
PB11.GPIO_Label=EMIT_2
PB11.Signal=GPIO_Output
PB12.GPIOParameters=GPIO_Label
PB12.GPIO_Label=EMIT_1
PB12.Signal=GPIO_Output
PB13.GPIOParameters=GPIO_Label
PB13.GPIO_Label=M2_FWD
PB13.Signal=GPIO_Output
PB14.GPIOParameters=GPIO_Label
PB14.GPIO_Label=M1_BCK
PB14.Signal=GPIO_Output
PB15.GPIOParameters=GPIO_Label
PB15.GPIO_Label=M2_BCK
PB15.Signal=GPIO_Output
PB4.GPIOParameters=GPIO_Label
PB4.GPIO_Label=BUTTON_1
PB4.Signal=GPIO_Input
PB5.GPIOParameters=GPIO_Label
PB5.GPIO_Label=EMIT_4
PB5.Signal=GPIO_Output
PB6.GPIOParameters=GPIO_Label
PB6.GPIO_Label=M2_ENC_B
PB6.Signal=S_TIM4_CH1
PB7.GPIOParameters=GPIO_Label
PB7.GPIO_Label=M2_ENC_A
PB7.Signal=S_TIM4_CH2
PB8.GPIOParameters=GPIO_Label
PB8.GPIO_Label=BUZZER
PB8.Signal=GPIO_Output
PB9.GPIOParameters=GPIO_Label
PB9.GPIO_Label=BUTTON_3
PB9.Signal=GPIO_Input
PC13-TAMPER-RTC.GPIOParameters=GPIO_PuPd,GPIO_Label
PC13-TAMPER-RTC.GPIO_Label=POWER_LED
PC13-TAMPER-RTC.GPIO_PuPd=GPIO_PULLDOWN
PC13-TAMPER-RTC.Signal=GPIO_Output
PC14-OSC32_IN.GPIOParameters=GPIO_Label
PC14-OSC32_IN.GPIO_Label=BUTTON_2
PC14-OSC32_IN.Signal=GPIO_Input
RCC.SYSCLKFreq_VALUE=36000000
RCC.SYSCLKSource=RCC_SYSCLKSOURCE_PLLCLK
board=custom
